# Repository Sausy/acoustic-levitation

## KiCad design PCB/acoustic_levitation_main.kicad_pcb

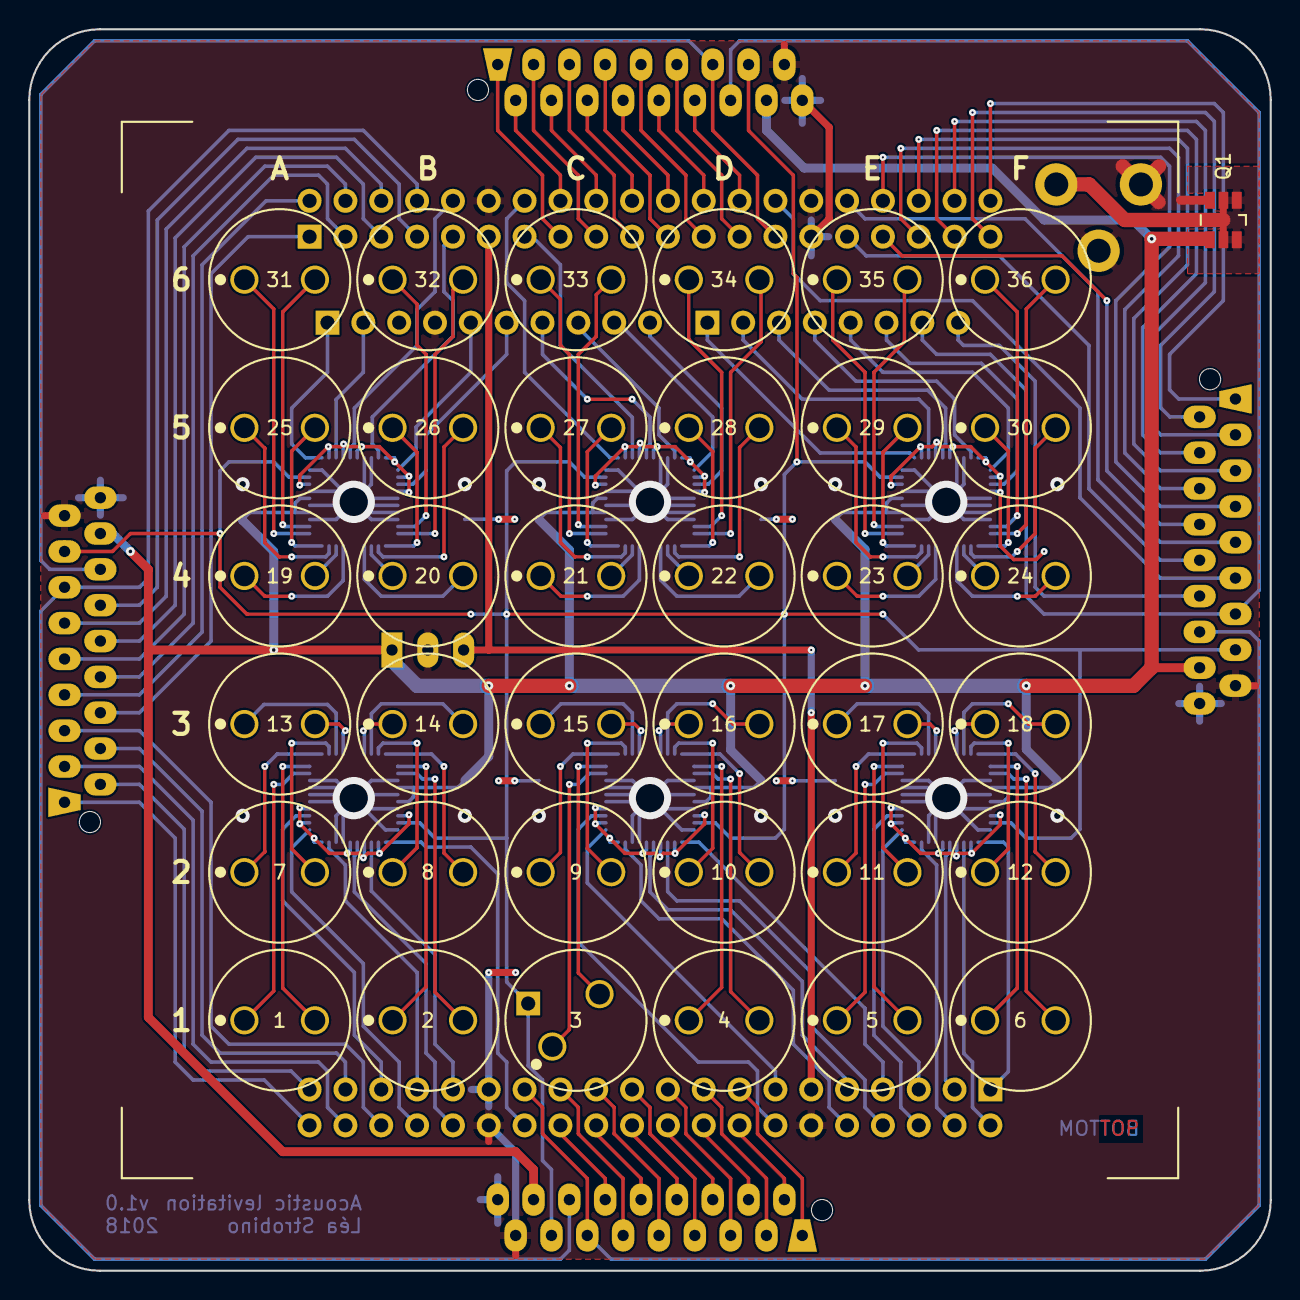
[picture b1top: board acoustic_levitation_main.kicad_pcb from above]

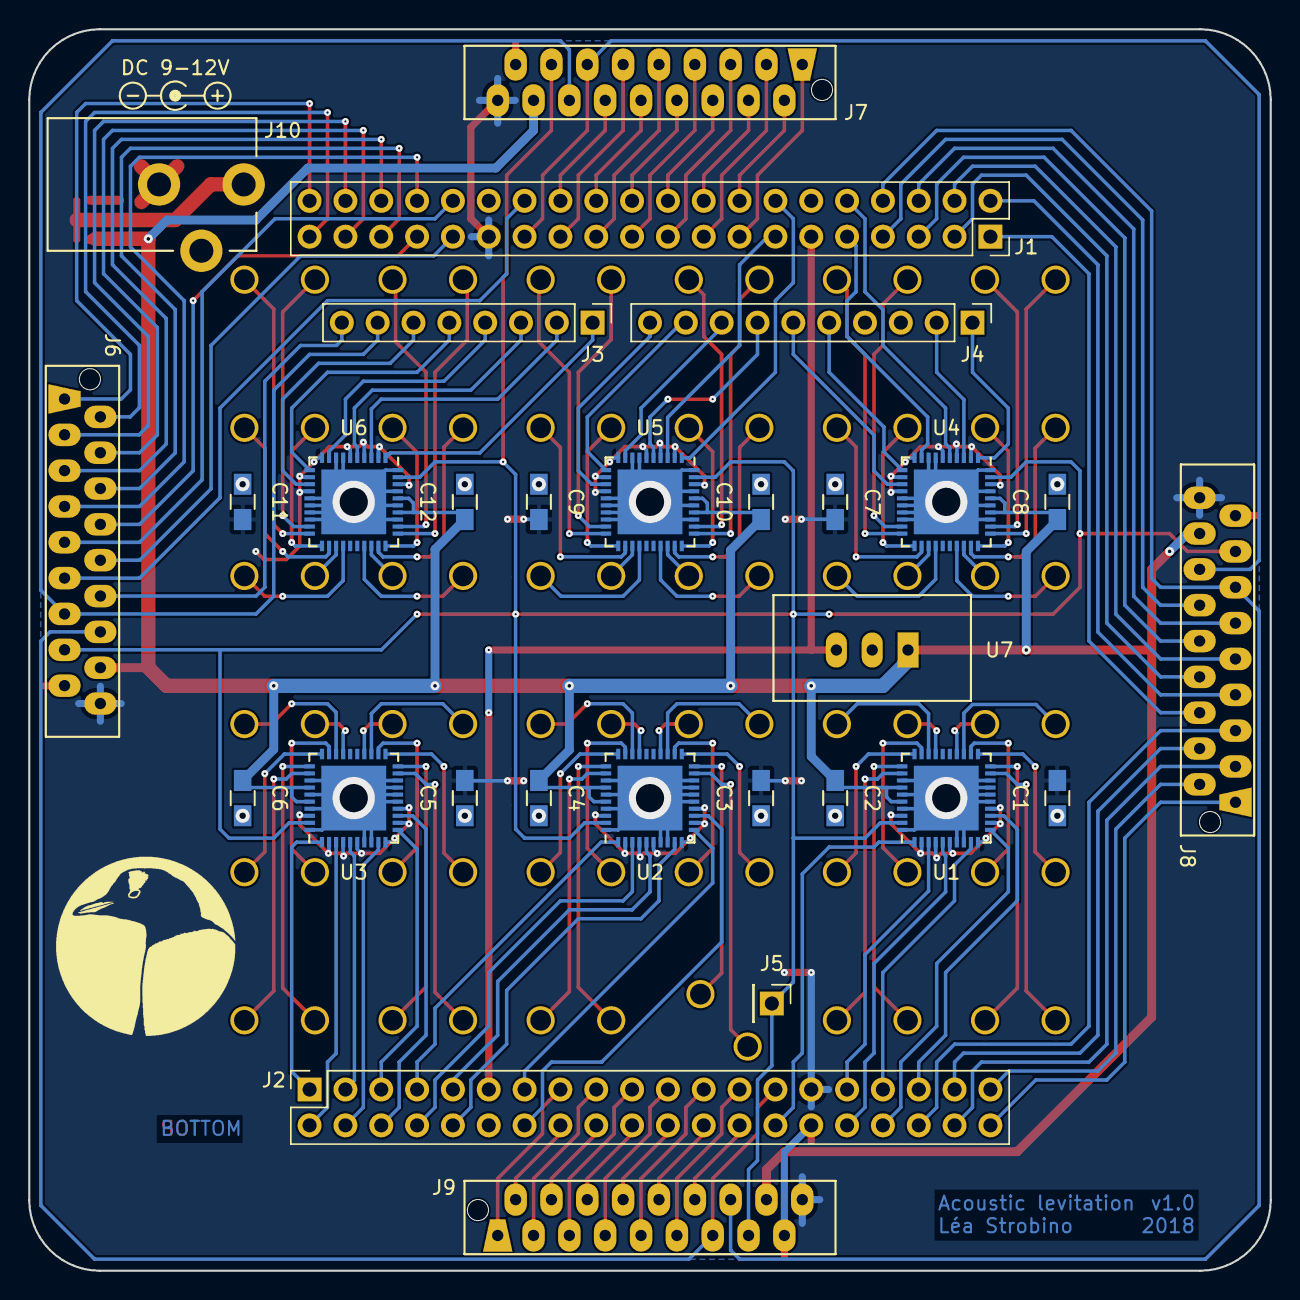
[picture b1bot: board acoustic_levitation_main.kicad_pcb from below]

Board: 2 copper layers, 88.0 x 88.0 mm, 66 parts (29 on the bottom side), 166 nets.

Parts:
C1, C2, C3, C4, C5, C6, C7, C8, C9, C10, C11, C12: 100n; C_0805_HandSoldering
J1: DE0-Nano-SoC: GPIO 0; Socket_Strip_Straight_2x20_Pitch2.54mm
J2: DE0-Nano-SoC: GPIO 1; Socket_Strip_Straight_2x20_Pitch2.54mm
J3: DE0-Nano-SoC: JP3; Pin_Header_Straight_1x08_Pitch2.54mm
J4: DE0-Nano-SoC: JP2; Pin_Header_Straight_1x10_Pitch2.54mm
J5: DE0-Nano-SoC: JP5[3]; Pin_Header_Straight_1x01_Pitch2.54mm
J6, J7, J8, J9: 8-215079-8; TE_8-215079-8
J10: PJ-102AH; CUI_PJ-102AH
Q1: Si3421DV; TSOP-6_2.9x1.5mm_Pitch0.95mm
TR1, TR2, TR3, TR4, TR5, TR6, TR7, TR8, TR9, TR10, TR11, TR12, TR13, TR14, TR15, TR16, TR17, TR18, TR19, TR20, TR21, TR22, TR23, TR24, TR25, TR26, TR27, TR28, TR29, TR30, TR31, TR32, TR33, TR34, TR35, TR36: MA40S4S; Murata_MA40S4S_TE_8134-HC-8P2
U1, U2, U3, U4, U5, U6: MAX17079; QFN-40-1EP_6x6mm_Pitch0.5mm_HandSoldering
U7: TSR2-2450; Traco_TSR2

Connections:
+3V3: C1.1, C3.1, C5.1, C7.1, C9.1, C11.1, J1.29, J2.29, J6.18, J7.18, J8.18, J9.18, U1.2, U1.4, U1.6, U1.10, U1.12, U1.14, U1.38, U2.2, U2.4, U2.6, U2.10, U2.12, U2.14, U2.38, U3.2, U3.4, U3.6, U3.10, U3.12, U3.14, U3.38, U4.2, U4.4, U4.6, U4.10, U4.12, U4.14, U4.38, U5.2, U5.4, U5.6, U5.10, U5.12, U5.14, U5.38, U6.2, U6.4, U6.6, U6.10, U6.12, U6.14, U6.38
+5V: J1.11, J2.11, U7.3
+12V: C2.1, C4.1, C6.1, C8.1, C10.1, C12.1, J6.16, J7.16, J8.16, J9.16, Q1.4, U1.34, U1.36, U2.34, U2.36, U3.34, U3.36, U4.34, U4.36, U5.34, U5.36, U6.34, U6.36, U7.1
+VDC: J10.1, Q1.1, Q1.2, Q1.5, Q1.6
/Enable: J5.1, J6.15, J7.15, J8.15, J9.15, U1.39, U2.39, U3.39, U4.39, U5.39, U6.39
/Piezo_A1: J2.28, U1.1
/Piezo_A2: J2.31, U1.3
/Piezo_A3: J2.32, U1.5
/Piezo_A4: J2.33, U1.9
/Piezo_A5: J2.34, U1.11
/Piezo_A6: J2.35, U1.13
/Piezo_B1: J2.7, U2.1
/Piezo_B2: J2.8, U2.3
/Piezo_B3: J2.9, U2.5
/Piezo_B4: J2.10, U2.9
/Piezo_B5: J2.13, U2.11
/Piezo_B6: J2.14, U2.13
/Piezo_C1: J2.1, U3.1
/Piezo_C2: J2.2, U3.3
/Piezo_C3: J2.3, U3.5
/Piezo_C4: J2.4, U3.9
/Piezo_C5: J2.5, U3.11
/Piezo_C6: J2.6, U3.13
/Piezo_D1: J4.1, U4.1
/Piezo_D2: J4.2, U4.3
/Piezo_D3: J1.10, U4.5
/Piezo_D4: J1.9, U4.9
/Piezo_D5: J4.5, U4.11
/Piezo_D6: J4.6, U4.13
/Piezo_E1: J1.14, U5.1
/Piezo_E2: J1.13, U5.3
/Piezo_E3: J4.7, U5.5
/Piezo_E4: J4.8, U5.9
/Piezo_E5: J4.9, U5.11
/Piezo_E6: J4.10, U5.13
/Piezo_F1: J3.1, U6.1
/Piezo_F2: J3.2, U6.3
/Piezo_F3: J3.3, U6.5
/Piezo_F4: J3.4, U6.9
/Piezo_F5: J3.5, U6.11
/Piezo_F6: J3.6, U6.13
/Wing_A1: J1.40, J6.1
/Wing_A2: J1.39, J6.2
/Wing_A3: J1.38, J6.3
/Wing_A4: J1.37, J6.4
/Wing_A5: J1.36, J6.5
/Wing_A6: J1.35, J6.6
/Wing_A7: J1.34, J6.7
/Wing_A8: J1.33, J6.8
/Wing_A9: J1.32, J6.9
/Wing_A10: J1.31, J6.10
/Wing_A11: J1.28, J6.11
/Wing_A12: J3.8, J6.12
/Wing_A13: J3.7, J6.13, J7.14
/Wing_A14: J2.27, J6.14, J9.13
/Wing_B1: J1.15, J7.1
/Wing_B2: J1.16, J7.2
/Wing_B3: J1.17, J7.3
/Wing_B4: J1.18, J7.4
/Wing_B5: J1.19, J7.5
/Wing_B6: J1.20, J7.6
/Wing_B7: J1.21, J7.7
/Wing_B8: J1.22, J7.8
/Wing_B9: J1.23, J7.9
/Wing_B10: J1.24, J7.10
/Wing_B11: J1.25, J7.11
/Wing_B12: J1.26, J7.12
/Wing_B13: J1.27, J7.13, J8.14
/Wing_C1: J2.40, J8.1
/Wing_C2: J2.39, J8.2
/Wing_C3: J2.38, J8.3
/Wing_C4: J2.37, J8.4
/Wing_C5: J2.36, J8.5
/Wing_C6: J1.1, J8.6
/Wing_C7: J1.2, J8.7
/Wing_C8: J1.3, J8.8
/Wing_C9: J1.4, J8.9
/Wing_C10: J1.5, J8.10
/Wing_C11: J1.6, J8.11
/Wing_C12: J1.7, J8.12
/Wing_C13: J1.8, J8.13, J9.14
/Wing_D1: J2.15, J9.1
/Wing_D2: J2.16, J9.2
/Wing_D3: J2.17, J9.3
/Wing_D4: J2.18, J9.4
/Wing_D5: J2.19, J9.5
/Wing_D6: J2.20, J9.6
/Wing_D7: J2.21, J9.7
/Wing_D8: J2.22, J9.8
/Wing_D9: J2.23, J9.9
/Wing_D10: J2.24, J9.10
/Wing_D11: J2.25, J9.11
/Wing_D12: J2.26, J9.12
GND: C1.2, C2.2, C3.2, C4.2, C5.2, C6.2, C7.2, C8.2, C9.2, C10.2, C11.2, C12.2, J1.12, J1.30, J2.12, J2.30, J4.4, J6.17, J7.17, J8.17, J9.17, J10.2, J10.3, Q1.3, U1.7, U1.8, U1.15, U1.16, U1.17, U1.18, U1.33, U1.35, U1.37, U1.40, U1.41, U2.7, U2.8, U2.15, U2.16, U2.17, U2.18, U2.33, U2.35, U2.37, U2.40, U2.41, U3.7, U3.8, U3.15, U3.16, U3.17, U3.18, U3.33, U3.35, U3.37, U3.40, U3.41, U4.7, U4.8, U4.15, U4.16, U4.17, U4.18, U4.33, U4.35, U4.37, U4.40, U4.41, U5.7, U5.8, U5.15, U5.16, U5.17, U5.18, U5.33, U5.35, U5.37, U5.40, U5.41, U6.7, U6.8, U6.15, U6.16, U6.17, U6.18, U6.33, U6.35, U6.37, U6.40, U6.41, U7.2
unnamed: TR1.1, U1.31
unnamed: TR1.2, U1.32
unnamed: TR2.1, U1.29
unnamed: TR2.2, U1.30
unnamed: TR3.1, U1.27
unnamed: TR3.2, U1.28
unnamed: TR4.1, U1.23
unnamed: TR4.2, U1.24
unnamed: TR5.1, U1.21
unnamed: TR5.2, U1.22
unnamed: TR6.1, U1.19
unnamed: TR6.2, U1.20
unnamed: TR7.1, U2.31
unnamed: TR7.2, U2.32
unnamed: TR8.1, U2.29
unnamed: TR8.2, U2.30
unnamed: TR9.1, U2.27
unnamed: TR9.2, U2.28
unnamed: TR10.1, U2.23
unnamed: TR10.2, U2.24
unnamed: TR11.1, U2.21
unnamed: TR11.2, U2.22
unnamed: TR12.1, U2.19
unnamed: TR12.2, U2.20
unnamed: TR13.1, U3.31
unnamed: TR13.2, U3.32
unnamed: TR14.1, U3.29
unnamed: TR14.2, U3.30
unnamed: TR15.1, U3.27
unnamed: TR15.2, U3.28
unnamed: TR16.1, U3.23
unnamed: TR16.2, U3.24
unnamed: TR17.1, U3.21
unnamed: TR17.2, U3.22
unnamed: TR18.1, U3.19
unnamed: TR18.2, U3.20
unnamed: TR19.1, U4.31
unnamed: TR19.2, U4.32
unnamed: TR20.1, U4.29
unnamed: TR20.2, U4.30
unnamed: TR21.1, U4.27
unnamed: TR21.2, U4.28
unnamed: TR22.1, U4.23
unnamed: TR22.2, U4.24
unnamed: TR23.1, U4.21
unnamed: TR23.2, U4.22
unnamed: TR24.1, U4.19
unnamed: TR24.2, U4.20
unnamed: TR25.1, U5.31
unnamed: TR25.2, U5.32
unnamed: TR26.1, U5.29
unnamed: TR26.2, U5.30
unnamed: TR27.1, U5.27
unnamed: TR27.2, U5.28
unnamed: TR28.1, U5.23
unnamed: TR28.2, U5.24
unnamed: TR29.1, U5.21
unnamed: TR29.2, U5.22
unnamed: TR30.1, U5.19
unnamed: TR30.2, U5.20
unnamed: TR31.1, U6.31
unnamed: TR31.2, U6.32
unnamed: TR32.1, U6.29
unnamed: TR32.2, U6.30
unnamed: TR33.1, U6.27
unnamed: TR33.2, U6.28
unnamed: TR34.1, U6.23
unnamed: TR34.2, U6.24
unnamed: TR35.1, U6.21
unnamed: TR35.2, U6.22
unnamed: TR36.1, U6.19
unnamed: TR36.2, U6.20

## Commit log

2019-02-13 added cmake
2019-02-13 recompiled rbf
2019-03-27 added div clock
2019-03-28 base functionen implemented and unstable working
2019-03-29 added output and rtc controll
